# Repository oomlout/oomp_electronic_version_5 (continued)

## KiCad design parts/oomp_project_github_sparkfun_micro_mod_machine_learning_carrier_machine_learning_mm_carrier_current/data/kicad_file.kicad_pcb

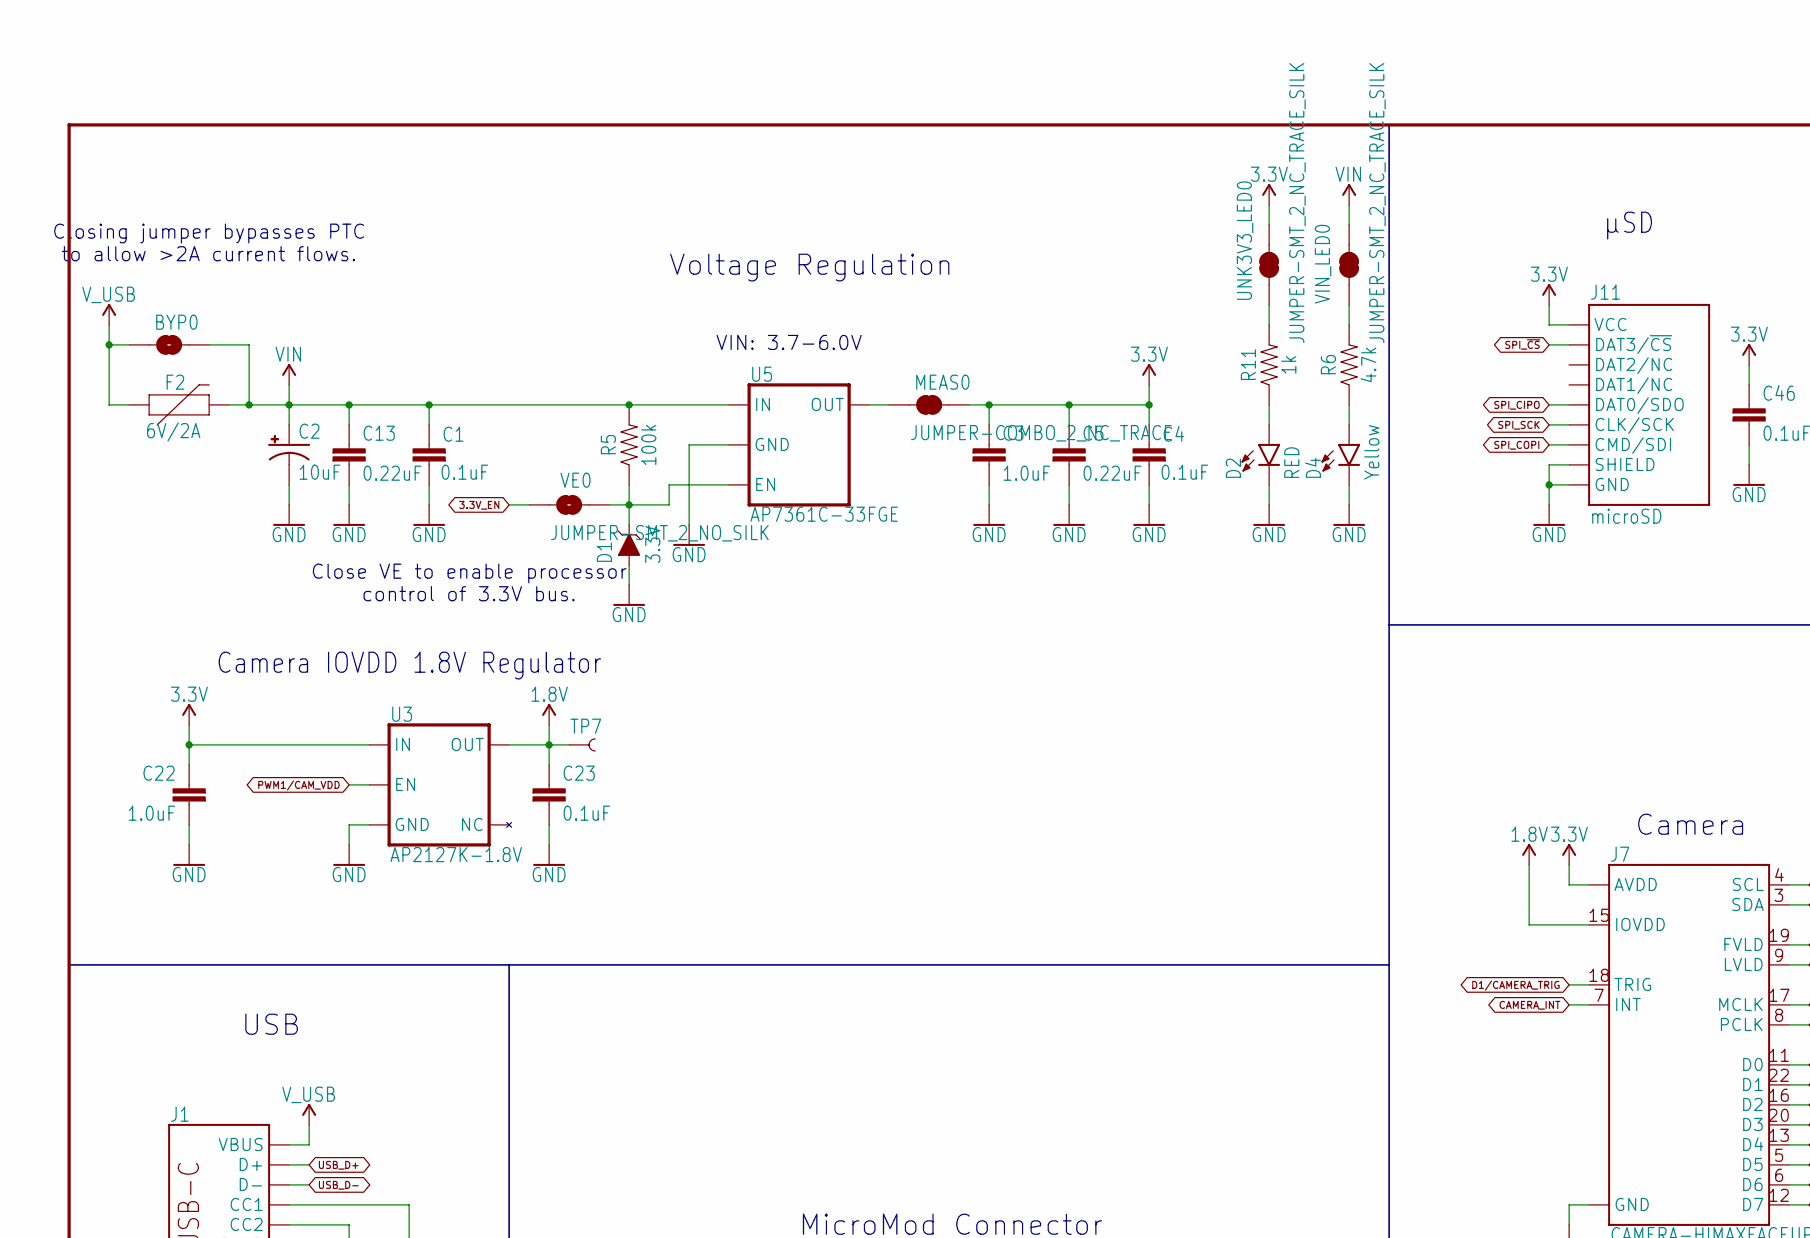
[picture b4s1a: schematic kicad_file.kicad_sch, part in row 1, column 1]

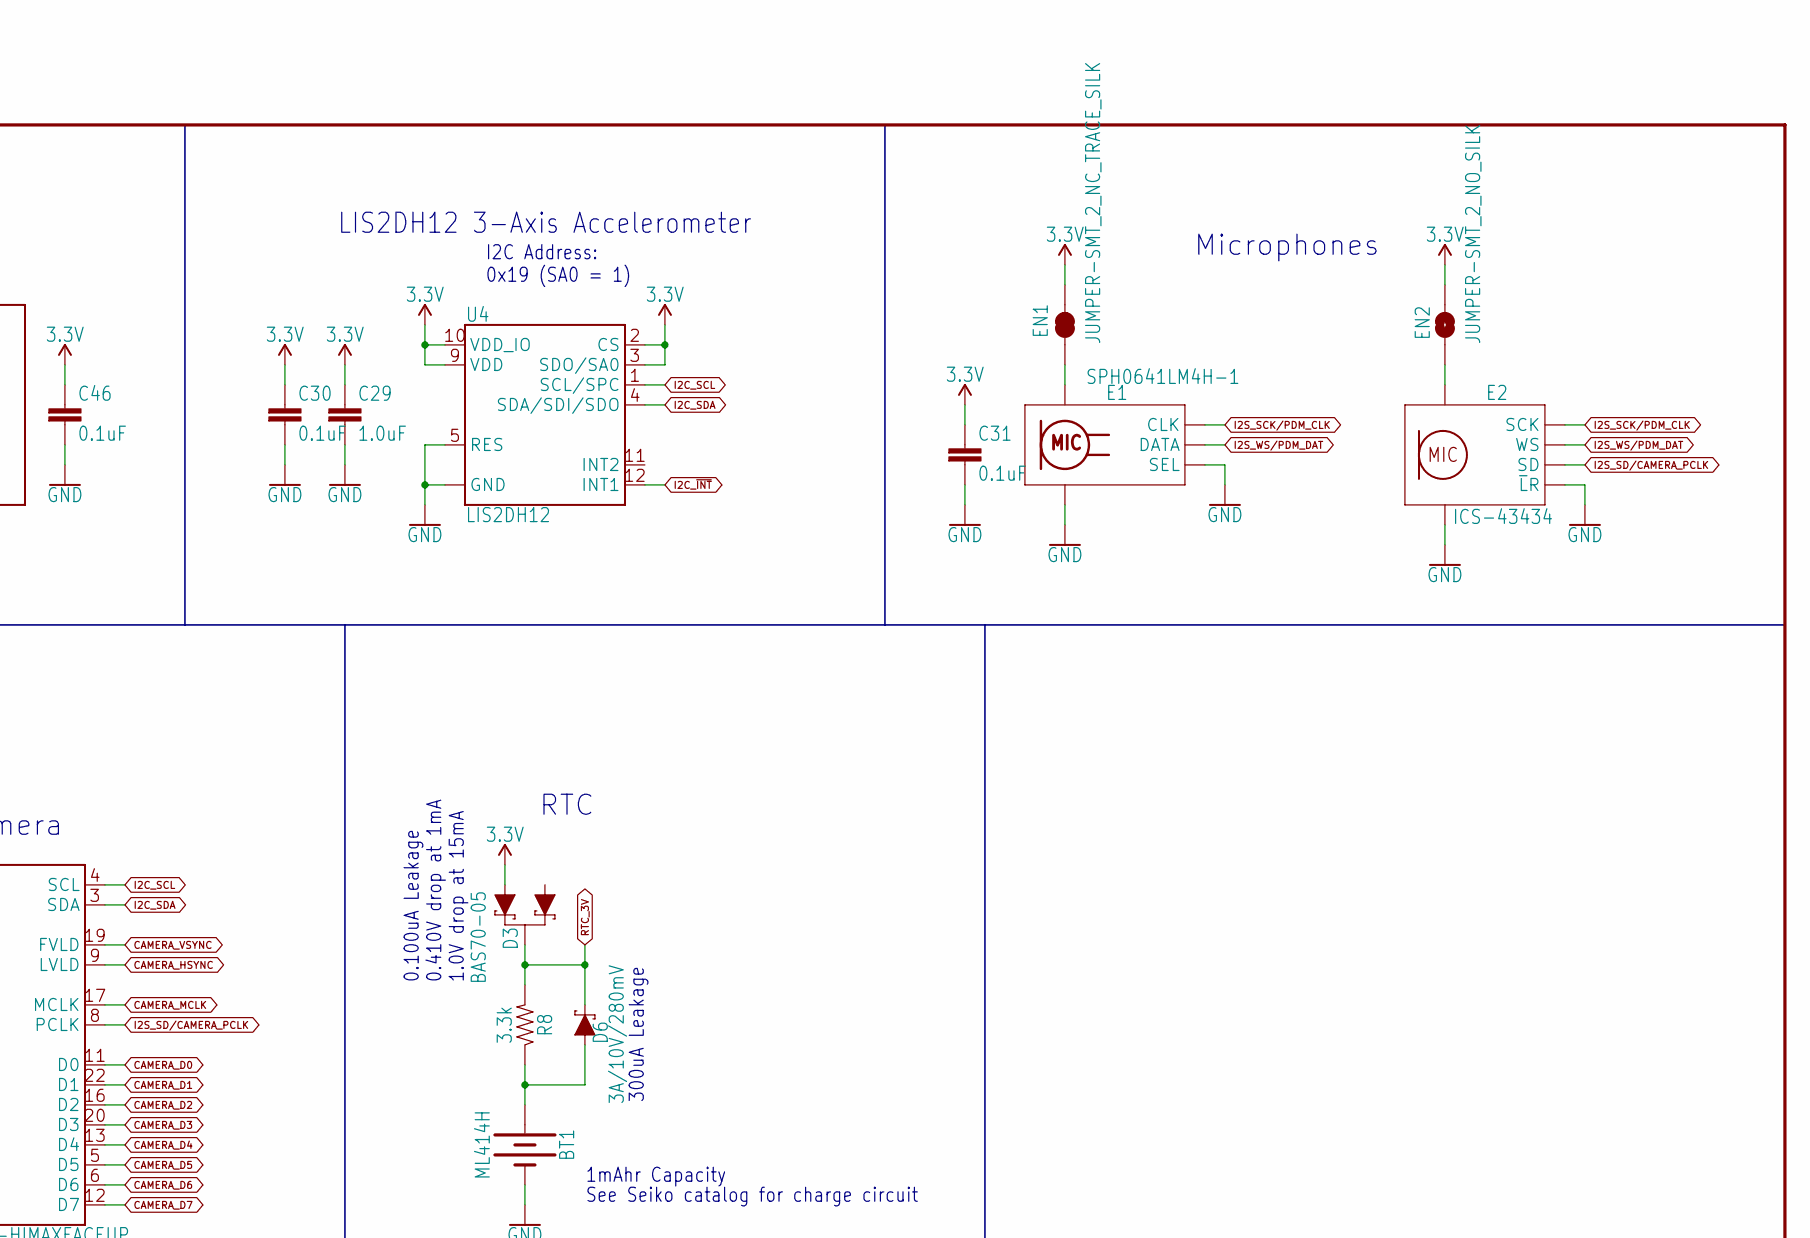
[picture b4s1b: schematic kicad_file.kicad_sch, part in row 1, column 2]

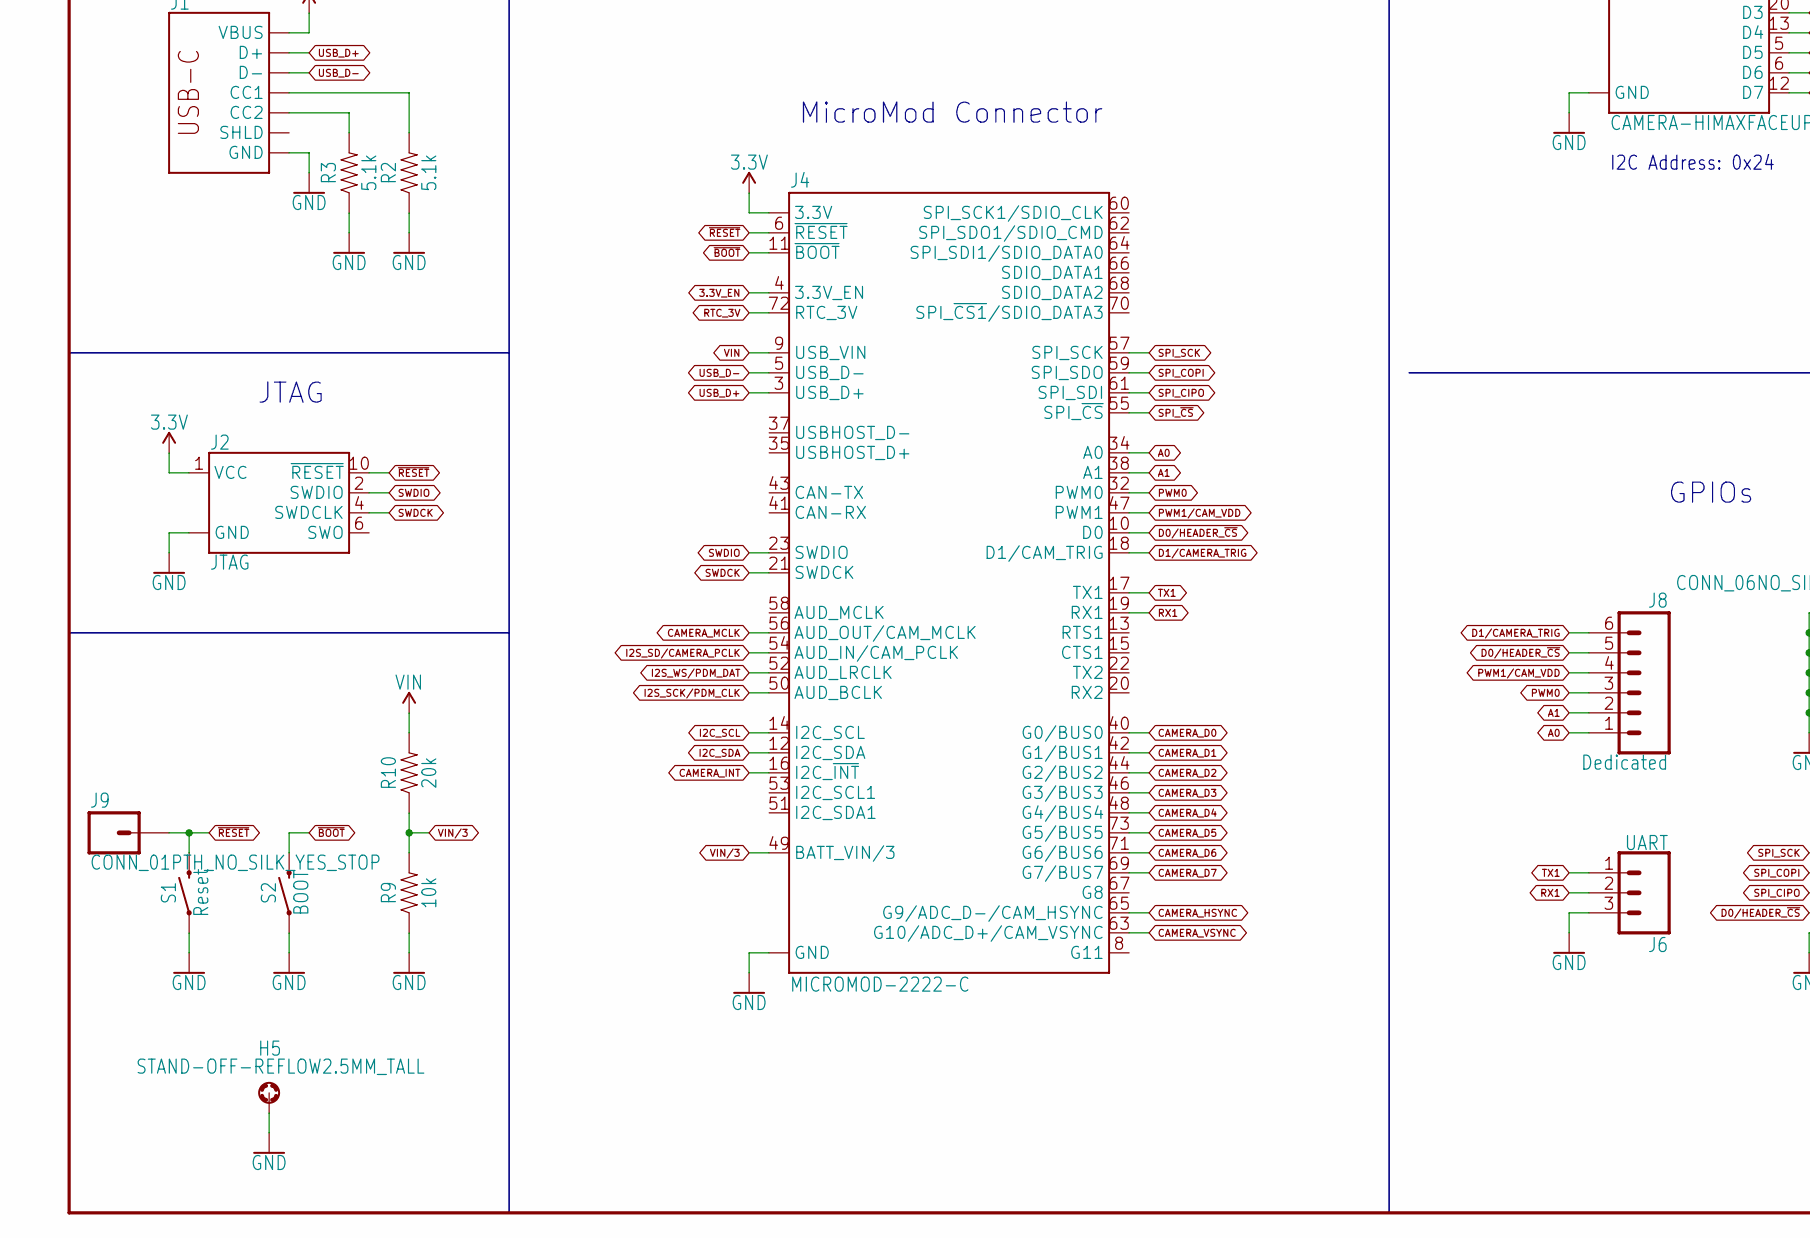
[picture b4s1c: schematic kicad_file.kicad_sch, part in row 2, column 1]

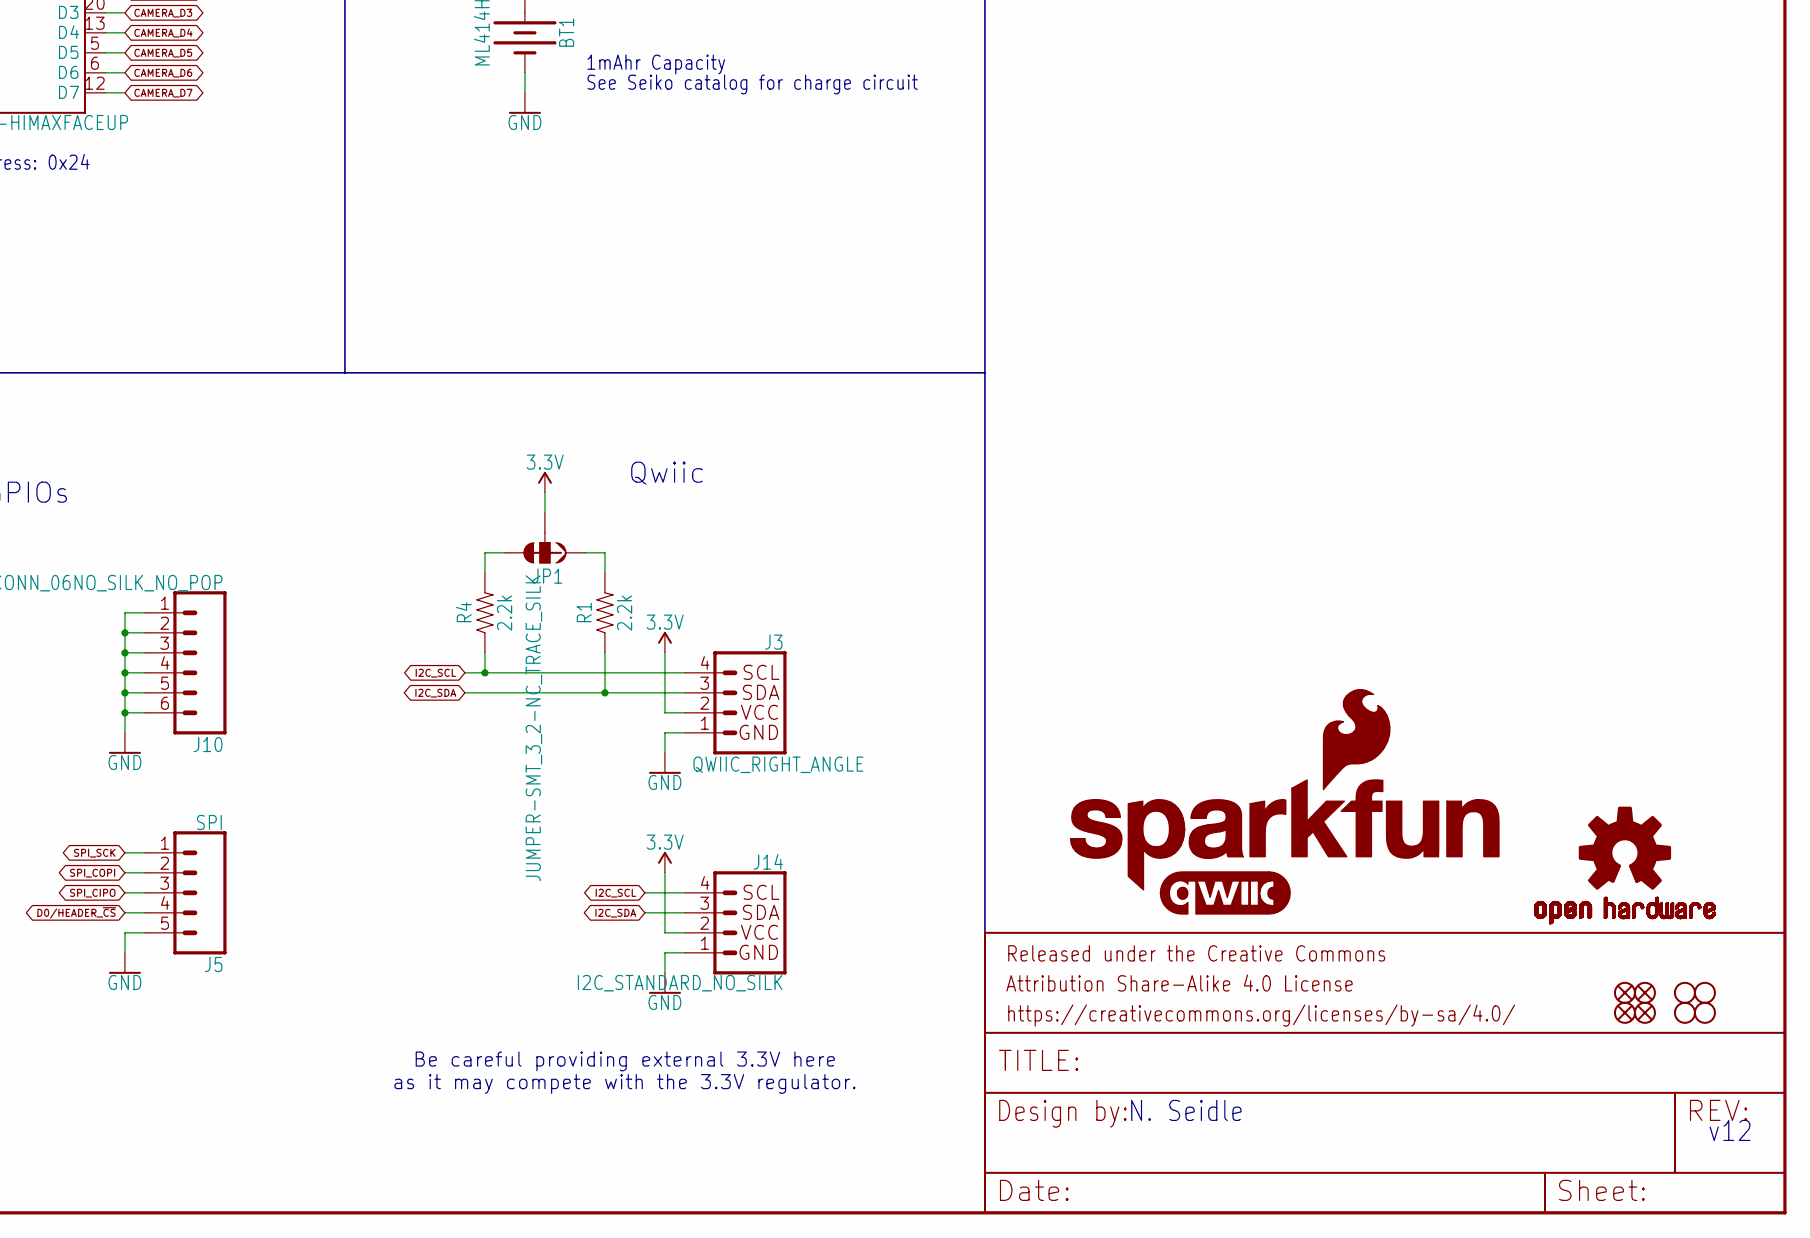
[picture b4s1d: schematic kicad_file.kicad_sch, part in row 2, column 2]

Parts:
BT1: ML414H; ML414H_IV01E
BYP0: JUMPER-SMT_2_NO_SILK; SMT-JUMPER_2_NO_SILK
C1, C4, C23, C30, C31, C46: 0.1uF; 0603
C2: 10uF; EIA3216
C3, C22, C29: 1.0uF; 0603
C5, C13: 0.22uF; 0603
D1: 3.3V; SOD-323
D2: RED; LED-0603
D3: BAS70-05; SOT23-3
D4: Yellow; LED-0603
D6: 3A/10V/280mV; SOD-323
E1: SPH0641LM4H-1; SPH0641LM4H-1_MICROPHONE
E2: ICS-43434
EN1: JUMPER-SMT_2_NC_TRACE_SILK; SMT-JUMPER_2_NC_TRACE_SILK
EN2: JUMPER-SMT_2_NO_SILK; SMT-JUMPER_2_NO_SILK
F2: 6V/2A; 1210
FD1, FD2, FD3, FD4: FIDUCIALUFIDUCIAL; FIDUCIAL-MICRO
FRAME1: FRAME-LEDGER; CREATIVE_COMMONS
H1, H2, H3, H4: STAND-OFF
H5: STAND-OFF-REFLOW2.5MM_TALL; STAND-OFF-REFLOW-M2.5
J1: USB_C_2-LAYER_PADS; USB-C-16P-2LAYER-PADS
J2: JTAG; 2X5-PTH-1.27MM
J3: QWIIC_RIGHT_ANGLE; JST04_1MM_RA
J4: MICROMOD-2222-C; M.2-CONNECTOR-E
J5: SPI; 1X05_NO_SILK
J6: UART; 1X03_NO_SILK
J7: CAMERA-HIMAXFACEUP; FPC05024-42201
J8: Dedicated; 1X06_NO_SILK
J9: CONN_01PTH_NO_SILK_YES_STOP; 1X01_NO_SILK
J10: CONN_06NO_SILK_NO_POP; 1X06_NO_SILK
J11: microSD; MICRO-SD-SOCKET
J14: I2C_STANDARD_NO_SILK; 1X04_NO_SILK
JP1: JUMPER-SMT_3_2-NC_TRACE_SILK; SMT-JUMPER_3_2-NC_TRACE_SILK
LOGO1: SFE_LOGO_NAME_FLAME.1_INCH; SFE_LOGO_NAME_FLAME_.1
LOGO2: QWIIC_LOGO_CONNECTOR; QWIIC_5.5MM
LOGO3: OSHW-LOGOMINI; OSHW-LOGO-MINI
MEAS0: JUMPER-COMBO_2_NC_TRACE; COMBO-JUMPER_2_NC_TRACE
R1, R4: 2.2k; 0603
R2, R3: 5.1k; 0603
R5: 100k; 0603
R6: 4.7k; 0603
R8: 3.3k; 0603
R9: 10k; 0603
R10: 20k; 0603
R11: 1k; 0603
S1: Reset; TACTILE_SWITCH_SMD_5.2MM
S2: BOOT; TACTILE_SWITCH_SMD_5.2MM
TP7: TEST-POINT3X5; PAD.03X.05
U3: AP2127K-1.8V; SOT23-5
U4: LIS2DH12; LGA-12-LISDH12; DIGIKEY 497-14851-2-ND
U5: AP7361C-33FGE; UDFN-8
UNK3V3_LED0: JUMPER-SMT_2_NC_TRACE_SILK; SMT-JUMPER_2_NC_TRACE_SILK
VE0: JUMPER-SMT_2_NO_SILK; SMT-JUMPER_2_NO_SILK
VIN_LED0: JUMPER-SMT_2_NC_TRACE_SILK; SMT-JUMPER_2_NC_TRACE_SILK

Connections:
1.8V: C23.1, J7.15 (IOVDD), TP7.P$1, U3.5 (OUT)
3.3V: C3.1, C4.1, C5.1, C22.1, C29.1, C30.1, C31.1, C46.1, D3.2 (A1), EN1.2, EN2.2, J2.1 (VCC), J3.2, J4.2 (3.3V), J4.74 (3.3V), J7.14 (AVDD), J7.21 (AVDD), J11.VCC, J14.2, JP1.2, MEAS0.2, MEAS0.4 (2), U3.1 (IN), U4.2 (CS), U4.3 (SDO/SA0), U4.9 (VDD), U4.10 (VDD_IO), UNK3V3_LED0.2
3.3V_EN: J4.4 (3.3V_EN), VE0.1
A0: J4.34 (A0), J8.1
A1: J4.38 (A1), J8.2
CAMERA_D0: J4.40 (G0/BUS0), J7.11 (D0)
CAMERA_D1: J4.42 (G1/BUS1), J7.22 (D1)
CAMERA_D2: J4.44 (G2/BUS2), J7.16 (D2)
CAMERA_D3: J4.46 (G3/BUS3), J7.20 (D3)
CAMERA_D4: J4.48 (G4/BUS4), J7.13 (D4)
CAMERA_D5: J4.73 (G5/BUS5), J7.5 (D5)
CAMERA_D6: J4.71 (G6/BUS6), J7.6 (D6)
CAMERA_D7: J4.69 (G7/BUS7), J7.12 (D7)
CAMERA_HSYNC: J4.65 (G9/ADC_D-/CAM_HSYNC), J7.9 (LVLD)
CAMERA_INT: J4.16 (I2C_~INT), J7.7 (INT)
CAMERA_MCLK: J4.56 (AUD_OUT/CAM_MCLK), J7.17 (MCLK)
CAMERA_VSYNC: J4.63 (G10/ADC_D+/CAM_VSYNC), J7.19 (FVLD)
D0/HEADER_~CS: J4.10 (D0), J5.4, J8.5
D1/CAMERA_TRIG: J4.18 (D1/CAM_TRIG), J7.18 (TRIG), J8.6
GND: BT1.-, C1.2, C2.-, C3.2, C4.2, C5.2, C13.2, C22.2, C23.2, C29.2, C30.2, C31.2, C46.2, D1.A, D2.C, D4.C, E1.2 (SEL), E1.3 (GND), E1.6 (GND), E1.7 (GND), E1.8 (GND), E2.2 (~LR), E2.3 (GND), E2.7 (GND), E2.8 (GND), E2.9 (GND), H5.1, J1.GND, J1.GND2 (GND), J2.3 (GND), J2.5 (GND), J2.9 (GND), J3.1, J4.1 (GND), J4.7 (GND), J4.33 (GND), J4.36 (GND), J4.39 (GND), J4.45 (GND), J4.75 (GND), J5.5, J6.3, J7.10 (GND), J7.23 (GND), J10.1, J10.2, J10.3, J10.4, J10.5, J10.6, J11.CD1 (SHIELD), J11.GND, J11.GND1 (GND), J11.GND3 (GND), J14.1, R2.1, R3.1, R9.1, S1.1, S1.2 (1), S2.1, S2.2 (1), U3.2 (GND), U4.5 (RES), U4.6 (GND), U4.7 (GND), U4.8 (GND), U5.4 (GND), U5.EP (GND)
I2C_SCL: J3.4, J4.14 (I2C_SCL), J7.4 (SCL), J14.4, R4.1, U4.1 (SCL/SPC)
I2C_SDA: J3.3, J4.12 (I2C_SDA), J7.3 (SDA), J14.3, R1.1, U4.4 (SDA/SDI/SDO)
I2C_~INT: U4.12 (INT1)
I2S_SCK/PDM_CLK: E1.4 (CLK), E2.4 (SCK), J4.50 (AUD_BCLK)
I2S_SD/CAMERA_PCLK: E2.6 (SD), J4.54 (AUD_IN/CAM_PCLK), J7.8 (PCLK)
I2S_WS/PDM_DAT: E1.1 (DATA), E2.1 (WS), J4.52 (AUD_LRCLK)
unnamed: R6.2, VIN_LED0.1
unnamed: JP1.3, R4.2
unnamed: JP1.1, R1.2
unnamed: E1.5 (VDD), EN1.1
unnamed: E2.5 (VDD), EN2.1
unnamed: R11.2, UNK3V3_LED0.1
unnamed: D2.A, R11.1
unnamed: D4.A, R6.1
unnamed: J1.A5 (CC1), R2.2
unnamed: J1.B5 (CC2), R3.2
unnamed: D1.C, R5.1, U5.5 (EN), VE0.2
unnamed: BT1.+, D6.A, R8.1
PWM0: J4.32 (PWM0), J8.3
PWM1/CAM_VDD: J4.47 (PWM1), J8.4, U3.3 (EN)
RTC_3V: D3.3 (C), D6.C, J4.72 (RTC_3V), R8.2
RX1: J4.19 (RX1), J6.2
SPI_CIPO: J4.61 (SPI_SDI), J5.3, J11.DO/DAT0 (DAT0/SDO)
SPI_COPI: J4.59 (SPI_SDO), J5.2, J11.DI/CMD (CMD/SDI)
SPI_SCK: J4.57 (SPI_SCK), J5.1, J11.SCLK (CLK/SCK)
SPI_~CS: J4.55 (SPI_~CS), J11.CS/DAT3 (DAT3/~CS)
SWDCK: J2.4 (SWDCLK), J4.21 (SWDCK)
SWDIO: J2.2 (SWDIO), J4.23 (SWDIO)
TX1: J4.17 (TX1), J6.1
USB_D+: J1.A6 (D+), J1.B6 (D+), J4.3 (USB_D+)
USB_D-: J1.A7 (D-), J1.B7 (D-), J4.5 (USB_D-)
VIN: BYP0.2, C1.1, C2.+, C13.1, F2.2, J4.9 (USB_VIN), R5.2, R10.2, U5.8 (IN), VIN_LED0.2
VIN/3: J4.49 (BATT_VIN/3), R9.2, R10.1
VREG_3.3V: MEAS0.1, MEAS0.3 (1), U5.1 (OUT)
V_USB: BYP0.1, F2.1, J1.VBUS1 (VBUS), J1.VBUS2 (VBUS)
~BOOT: J4.11 (~BOOT), S2.3 (2), S2.4 (2)
~RESET: J2.10 (~RESET), J4.6 (~RESET), J9.1, S1.3 (2), S1.4 (2)

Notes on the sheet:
Microphones
Camera IOVDD 1.8V Regulator
USB
Be careful providing external 3.3V here as it may compete with the 3.3V regulator.
I2C Address: 0x19 (SA0 = 1)
μSD
See Seiko catalog for charge circuit
GPIOs
VIN: 3.7-6.0V
Close VE to enable processor control of 3.3V bus.
300uA Leakage
MicroMod Connector
Closing jumper bypasses PTC to allow >2A current flows.
Qwiic
LIS2DH12 3-Axis Accelerometer
JTAG
Camera
Voltage Regulation
1mAhr Capacity
N. Seidle
0.100uA Leakage 0.410V drop at 1mA 1.0V drop at 15mA
I2C Address: 0x24
v12
RTC

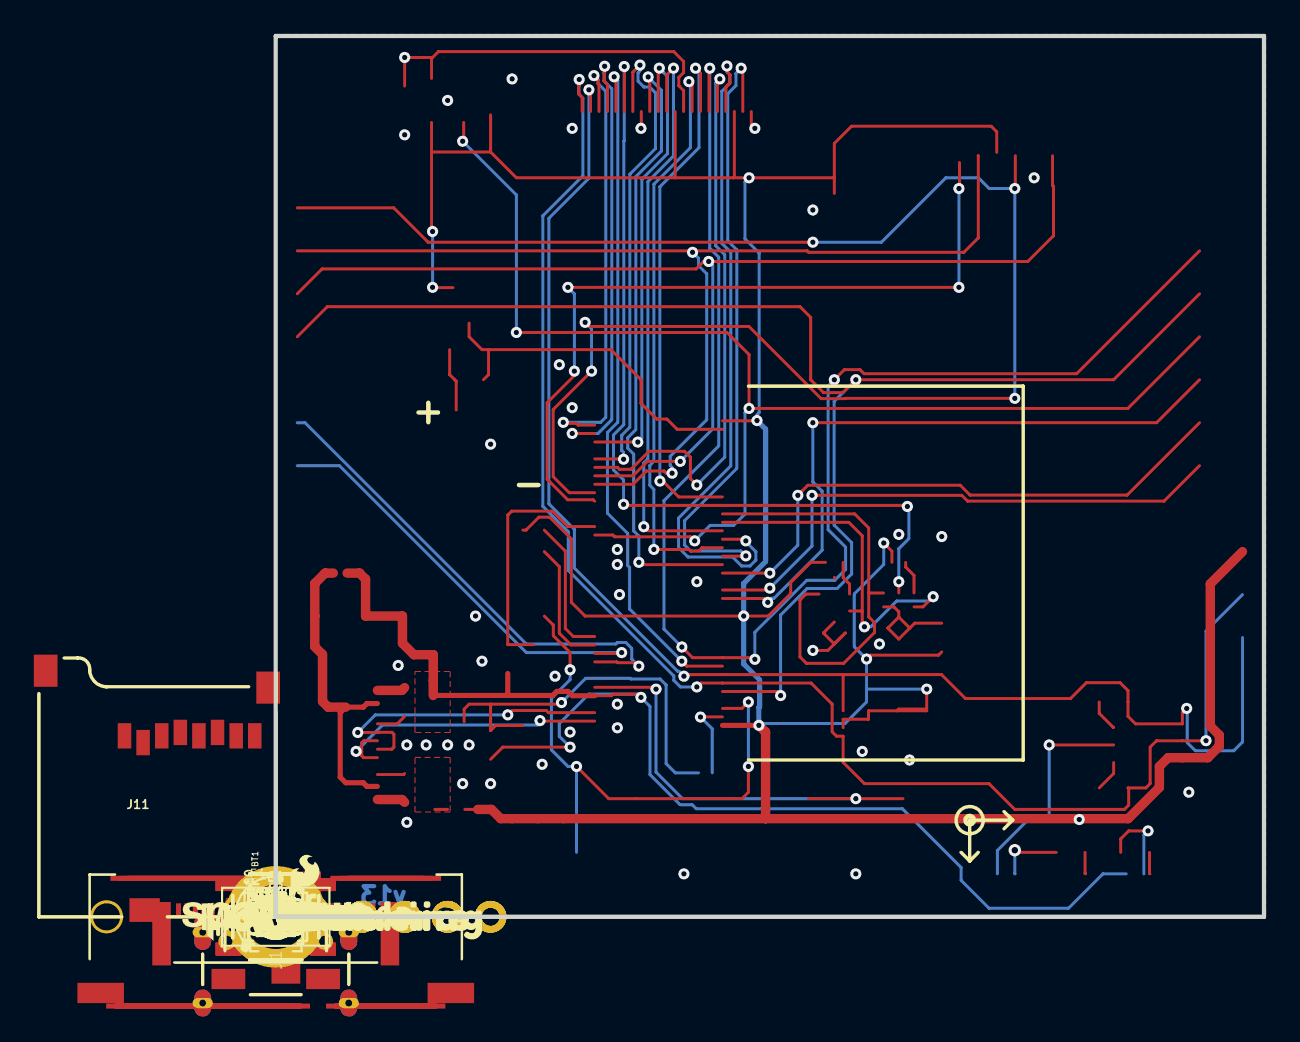
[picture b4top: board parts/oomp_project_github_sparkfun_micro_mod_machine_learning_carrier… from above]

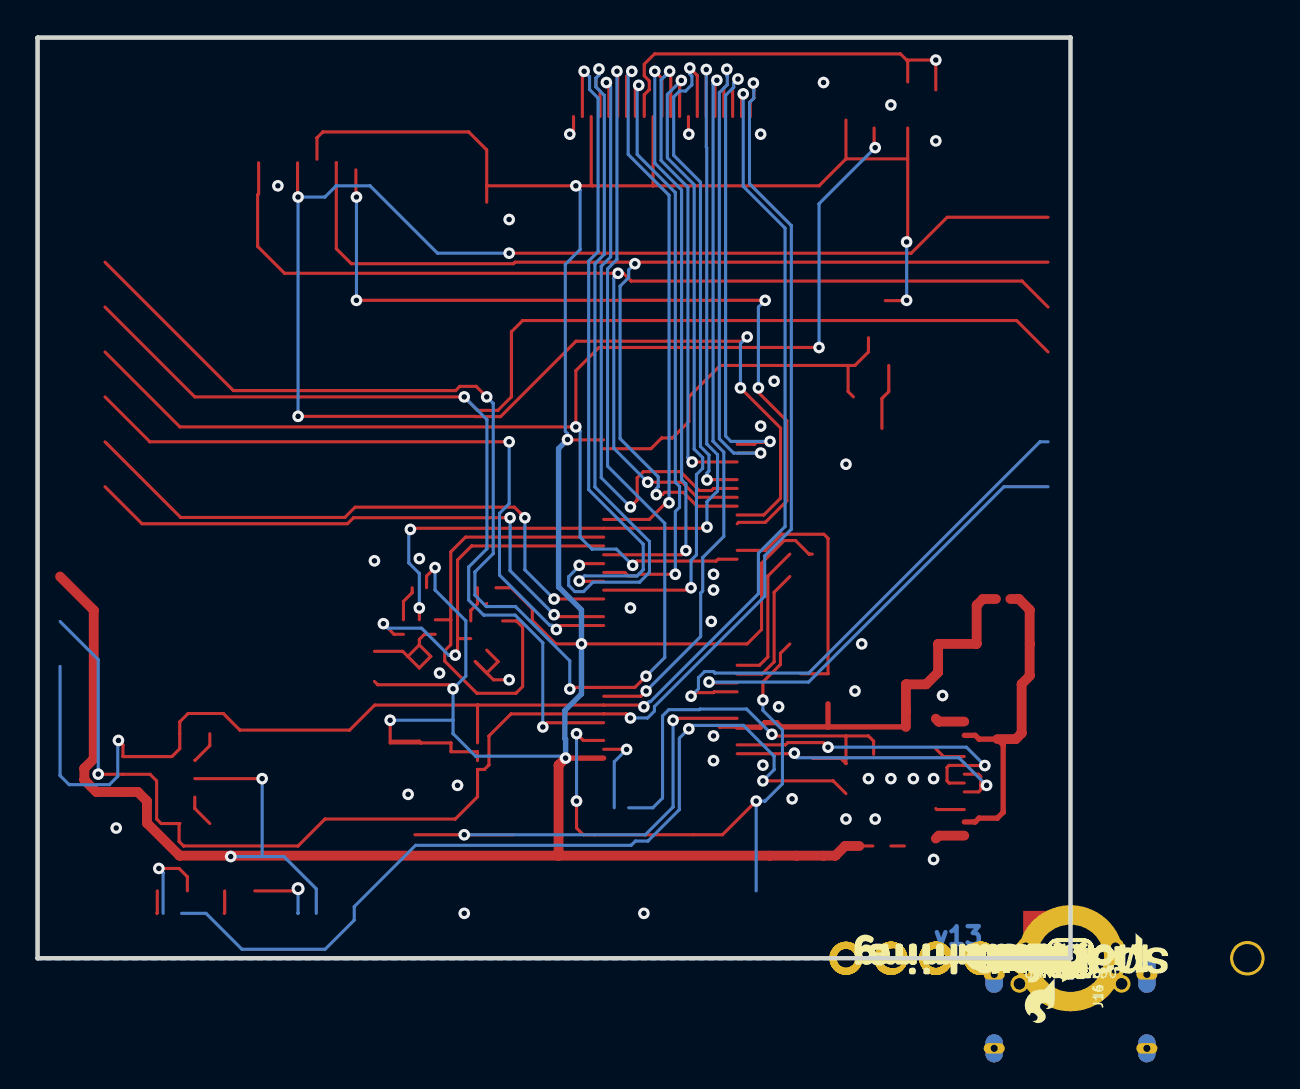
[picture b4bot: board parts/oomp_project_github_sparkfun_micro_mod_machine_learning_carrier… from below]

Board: 2 copper layers, 58.4 x 52.1 mm, 138 parts (36 on the bottom side), 56 nets.

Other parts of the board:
LOGO4: SFE_LOGO_NAME_FLAME.1_INCH; SFE_LOGO_NAME_FLAME_.1
U$1: #EN1#3
U$2: #EN2#4
U$3: CAMERA0
U$4: #3V3#0
U$5: MICS0
U$6, U$7: #A0#5
U$8, U$9: #A1#4
U$10, U$25: #D0#1
U$11, U$12, U$15, U$16: #GND#0
U$13, U$14: #3V3#1
U$17: #RST#1
U$18: #VE#0
U$19: #MEAS#2
U$20: #VIN#1
U$21: SWD0
U$22: FACE_UP0
U$23: #I�C#0
U$24, U$34: MICROMOD_LOGO_.35
U$26, U$37: MACHINE0
U$27, U$30: LEARNING1
U$28: MICROSD0
U$29, U$31: #D1#0
U$32, U$41: #PWM0#3
U$33: #BYP#1
U$35, U$68: ##CS##3
U$36: 3V37
U$38: 22223
U$39: ACCEL4
U$40: BOOT5
U$42, U$49: #PWM1#2
U$43, U$44: #SCL#3
U$45: RESET6
U$46: VIN8
U$47: X1
U$48: Y2
U$50, U$51: #SDA#2
U$52: Z0
U$69, U$70: #CIPO#2
U$71, U$72: #COPI#1
U$73, U$74, U$81, U$82: #GND#4
U$75, U$76: #RX1#6
U$77, U$78: #SCK#0
U$79, U$80: #TX1#5

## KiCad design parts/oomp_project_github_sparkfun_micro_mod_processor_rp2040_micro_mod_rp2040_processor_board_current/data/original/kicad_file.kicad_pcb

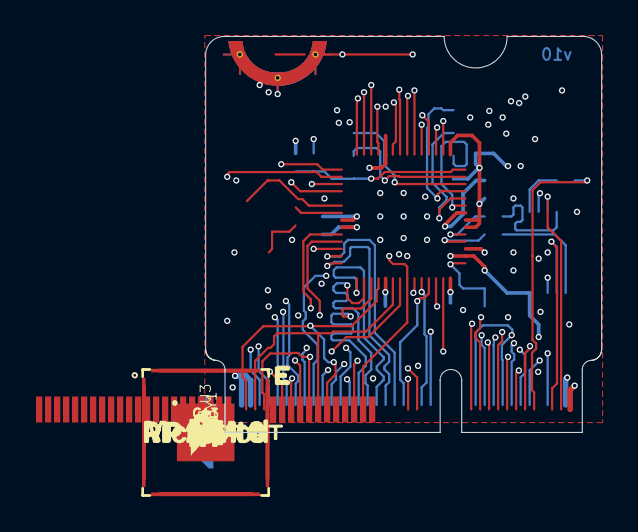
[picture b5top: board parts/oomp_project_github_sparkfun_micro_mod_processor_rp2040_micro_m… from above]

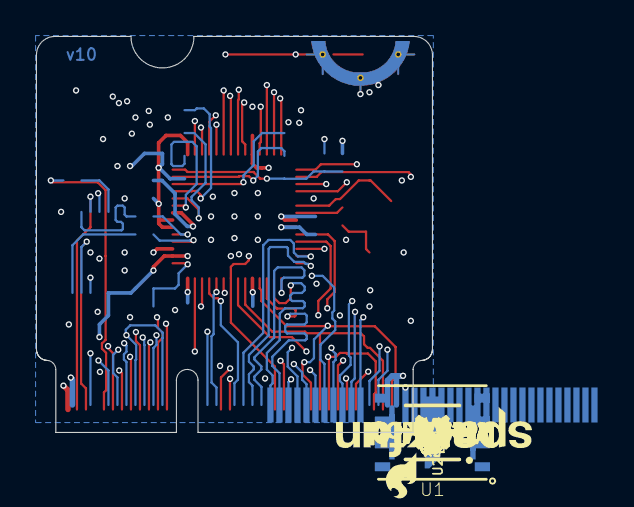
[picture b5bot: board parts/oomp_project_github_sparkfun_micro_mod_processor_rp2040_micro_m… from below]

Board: 4 copper layers, 22.0 x 22.0 mm, 47 parts (28 on the bottom side), 58 nets.

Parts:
C1, C3, C4, C15: 2.2uF; 0402-TIGHT
C2, C5, C6, C7, C8, C9, C10, C12, C14, C29: 0.1uF; 0402-TIGHT
C11, C13: 15pF; 0402-TIGHT
D2: BLUE; LED-0603
FD1, FD2, FD3, FD4: FIDUCIALUFIDUCIAL; FIDUCIAL-MICRO
FRAME1: FRAME-LEDGER; CREATIVE_COMMONS
J1: MICROMOD-2222; M.2-CARD-E-22
LOGO1: SFE_LOGO_NAME_FLAME.1_INCH; SFE_LOGO_NAME_FLAME_.1
LOGO2: SFE_LOGO_FLAME.1_INCH; SFE_LOGO_FLAME_.1
LOGO3: OSHW-LOGOMINI; OSHW-LOGO-MINI
LOGO4: SPECIAL_INSTRUCTIONS-ORDERING; ORDERING_INSTRUCTIONS
R1, R8, R9, R18: 1k; 0402-TIGHT
R2: 200OHM-0402T-1/16W-1%; 0402-TIGHT
R4, R5: 10k; 0402-TIGHT
R10, R11: 27; 0402-TIGHT
U1: W25QXX128MBIT; WSON-8-6X5-SKINNY_CENTERPAD
U2: FSUSB30MUX_MSOP10; MSOP10
U3: RP2040; QFN-56
U$1, U$7: MICROMOD_MI_LOGO_.35
U$3, U$12: MICROMOD_LOGO_.3
U$4, U$9: RP20400
U$11: STAT0
Y1: 12MHz; CRYSTAL-SMD-2X2.5MM

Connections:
1.1V: C3.1, C12.1, C14.1, U3.23, U3.45, U3.50
3.3V: C2.1, C4.1, C5.1, C6.1, C7.1, C8.1, C9.1, C10.1, C15.1, C29.1, J1.2, J1.72, J1.74, R2.2, R4.2, U1.8, U2.10, U3.1, U3.10, U3.22, U3.33, U3.42, U3.44, U3.48, U3.49
A0: J1.34, U3.38
A1: J1.38, U3.39
ADC_VDD: C1.1, R2.1, U3.43
BATT_VIN/3: J1.49, U3.41
BOOT: J1.11, R9.2
CTS1/AUD_LRCLK: J1.15, J1.52, U3.4
D0: J1.10, U3.8
D1: J1.18, U3.9
G0: J1.40, U3.27
G1: J1.42, U3.28
G2: J1.44, U3.29
G3: J1.46, U3.30
G9: J1.65, U3.40
GND: C1.2, C2.2, C3.2, C4.2, C5.2, C6.2, C7.2, C8.2, C9.2, C10.2, C11.1, C12.2, C13.1, C14.2, C15.2, C29.2, D2.C, J1.1, J1.7, J1.33, J1.36, J1.39, J1.45, J1.75, J1.GND1, J1.GND2, J1.GND3, R5.1, U1.4, U2.5, U2.9, U3.19, U3.EPAD
I2C_~INT/TX2: J1.16, J1.22, U3.11
LED_BUILTIN/G10: J1.63, R1.2, U3.37
unnamed: D2.A, R1.1
unnamed: R8.2, U3.21
unnamed: C13.2, U3.20, Y1.P3
unnamed: C11.2, R8.1, Y1.P1
PWM0: J1.32, U3.16
PWM1/AUD_MCLK: J1.47, J1.58, U3.36
QSPI-0: U1.5, U3.53
QSPI-1: U1.2, U3.55
QSPI-2: U1.3, U3.54
QSPI-3: U1.7, U3.51
QSPI-CLK: U1.6, U3.52
QSPI-CS: R4.1, R9.1, U1.1, U3.56
RP_D1+: R10.2, U3.47
RP_D1-: R11.2, U3.46
RP_D+: R10.1, U2.4
RP_D-: R11.1, U2.6
RTS1/AUD_BCLK: J1.13, J1.50, U3.5
RX1: J1.19, U3.3
SCL: J1.14, U3.7
SDA: J1.12, U3.6
SDIO_DAT1/AUD_IN: J1.54, J1.66, U3.14
SDIO_DAT2/AUD_OUT: J1.56, J1.68, U3.13
SPI_CIPO1/SDIO_DAT0: J1.64, U3.15
SPI_CIPO/G4: J1.48, J1.61, U3.31
SPI_COPI1/SDIO_CMD: J1.62, U3.18
SPI_COPI/G7: J1.59, J1.69, U3.35
SPI_SCK1/SDIO_CLK: J1.60, U3.17
SPI_SCK/G6: J1.57, J1.71, U3.34
SPI_~CS1/SDIO_DAT3/RX2: J1.20, J1.70, U3.12
SPI_~CS/G5: J1.55, J1.73, U3.32
SWDCK: J1.21, U3.24
SWDIO: J1.23, U3.25
TX1: J1.17, U3.2
USBHOST_D+: J1.35, U2.2
USBHOST_D-: J1.37, U2.8
USB_D+: J1.3, U2.3
USB_D-: J1.5, U2.7
USB_MUX_SIG: R5.2, R18.2, U2.1
USB_VIN: J1.9, R18.1
~RESET: J1.6, U3.26
